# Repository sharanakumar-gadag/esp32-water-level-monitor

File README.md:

# ESP32 Water Level Monitor

A 4-level water monitoring system built around an ESP32, with a custom KiCad-designed PCB, four float level sensors, an OLED display and a buck converter power supply.

## Features
- Detects water level using 4 float sensors (S1 to S4)
- Live status on a 1.3" I2C OLED: each sensor shows WET or DRY, plus the overall level (L:0 to L:4)
- Custom PCB designed in KiCad, with Gerber files included
- Powered from 12V through a buck converter (HW-688 module, 5V output)

## Hardware
| Component | Details |
|---|---|
| Microcontroller | ESP32 DevKit V1 (30-pin) |
| Sensors | 4 x float level sensors (connectors J2, J3, J5, J6) |
| Display | 1.3" I2C OLED (SH1106) |
| Power | 12V input, HW-688 buck converter module (5V output) |
| PCB | Custom 2-layer board designed in KiCad |

## Pin connections
| Signal | ESP32 pin |
|---|---|
| Sensor 1 to 4 | GPIO 25, 26, 27, 32 (common GND) |
| OLED SDA | GPIO 21 |
| OLED SCL | GPIO 22 |
| OLED VCC | 3.3V |

## Photos
**OLED output (all 4 sensors wet, level 4)**

**Assembled PCB**

## PCB design

## Repository structure
- `firmware/`: ESP32 code (Arduino IDE)
- `hardware/kicad-project/`: KiCad project files
- `hardware/schematic/`: schematic
- `hardware/gerber/`: Gerber and drill files for PCB fabrication
- `hardware/pcb-images/`: PCB layout and 3D view
- `images/`: project photos

## How it works
Each float sensor closes a contact when the water reaches it. The ESP32 reads the four inputs and counts how many sensors are wet. That count is shown as the water level (L:0 to L:4) on the OLED, along with the state of each sensor.

## Getting started
1. Open `firmware/water_level_monitor/water_level_monitor.ino` in the Arduino IDE.
2. Install the libraries Adafruit GFX and Adafruit SH110X.
3. Select your ESP32 board and upload.
4. Connect the sensors to J2, J3, J5 and J6 and power the board with 12V.

## Author
Sharanakumar Gadag, Electronics and Communication Engineering

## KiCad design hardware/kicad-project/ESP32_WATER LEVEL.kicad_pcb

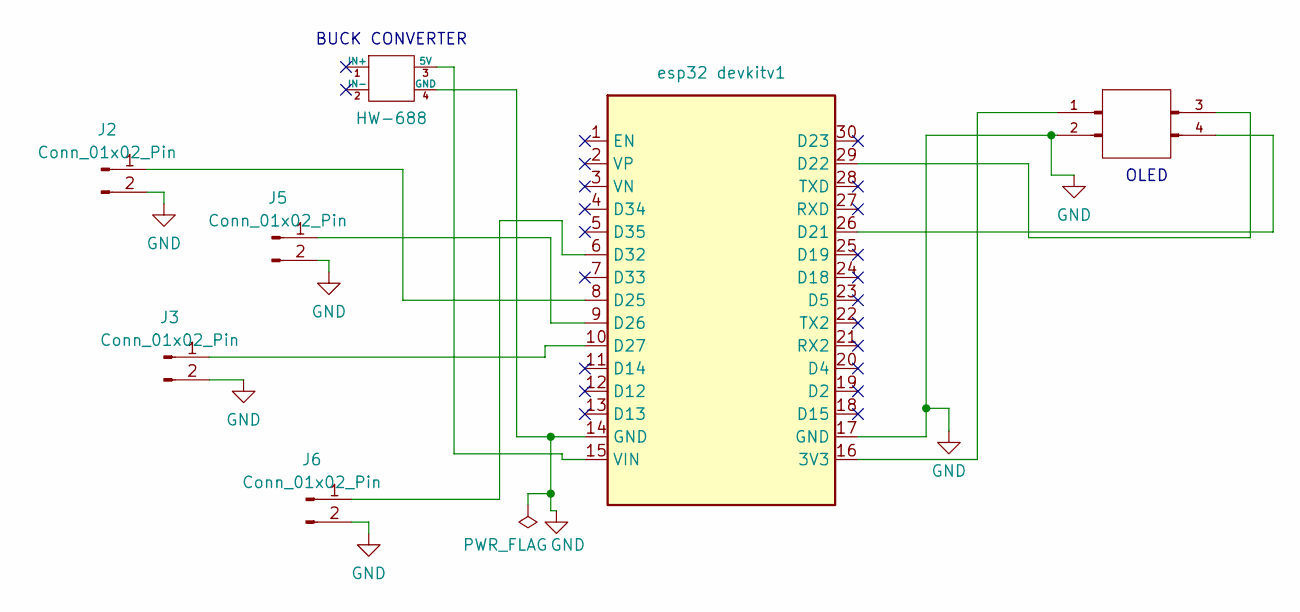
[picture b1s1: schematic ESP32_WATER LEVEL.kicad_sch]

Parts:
J1: OLED_1.3_I2C; PinHeader_1x04_P2.54mm_Vertical
J2, J3, J5, J6: Conn_01x02_Pin; PinHeader_1x02_P2.54mm_Vertical
U1: HW-688
U9: Lib:ESP32_DEVKIT_V1; ESP32_DEVKIT_V1

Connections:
GND: J1.2 (GND), J2.2, J3.2, J5.2, J6.2, U1.4 (GND), U9.14 (GND), U9.17 (GND)
unnamed: J1.3 (SCK), U9.29 (D22)
unnamed: J1.4 (SDA), U9.26 (D21)
unnamed: J1.1 (VDD), U9.16 (3V3)
unnamed: J2.1, U9.8 (D25)
unnamed: J3.1, U9.10 (D27)
unnamed: J5.1, U9.9 (D26)
unnamed: J6.1, U9.6 (D32)
unnamed: U1.3 (5V), U9.15 (VIN)

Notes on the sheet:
OLED
BUCK CONVERTER

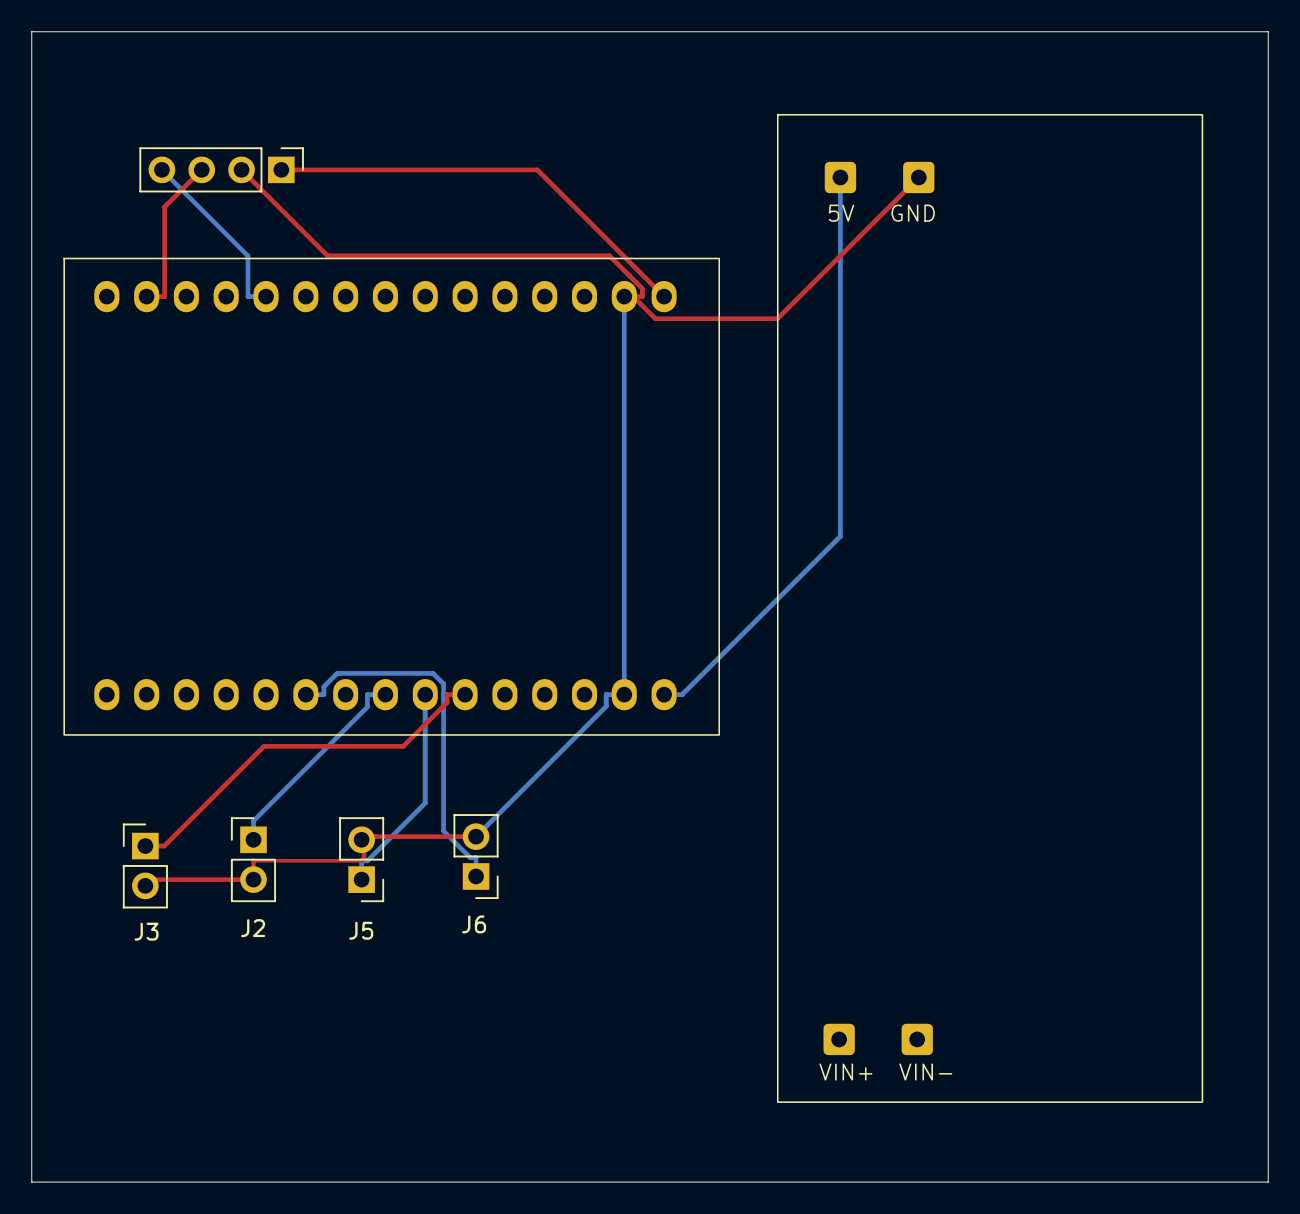
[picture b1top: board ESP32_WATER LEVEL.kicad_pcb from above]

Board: 2 copper layers, 78.9 x 73.4 mm, 7 parts (0 on the bottom side), 9 nets.
